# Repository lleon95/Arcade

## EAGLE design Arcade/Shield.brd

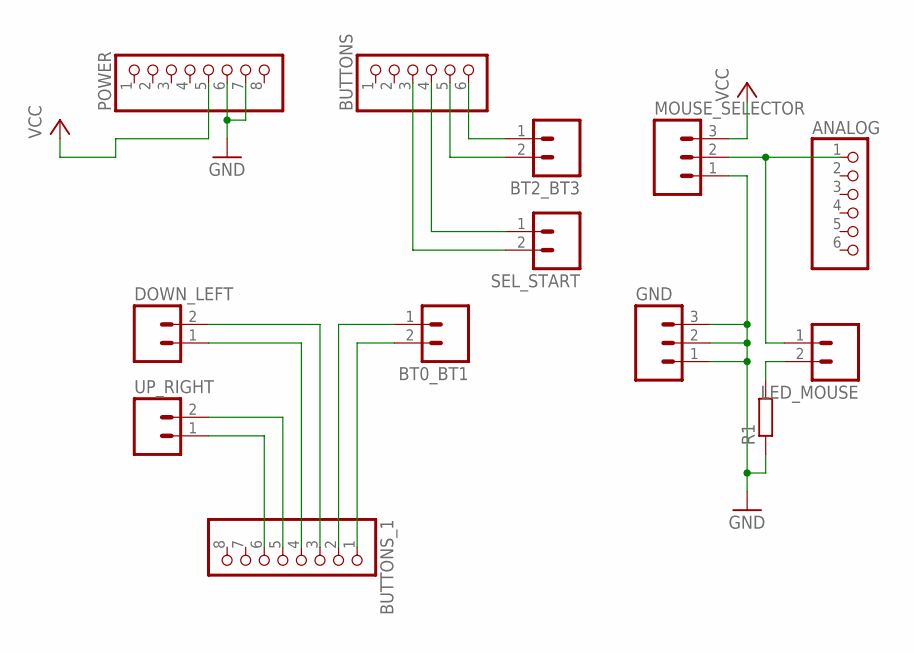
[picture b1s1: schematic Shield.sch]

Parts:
ANALOG: PINHD-1X6; 1X06
BT0_BT1, BT2_BT3: M023.5MM; SCREWTERMINAL-3.5MM-2
BUTTONS: PINHD-1X6; 1X06
BUTTONS_1: PINHD-1X8BIG; 1X08-BIG
DOWN_LEFT: M023.5MM; SCREWTERMINAL-3.5MM-2
GND: M03SCREW; SCREWTERMINAL-3.5MM-3
LED_MOUSE: M023.5MM; SCREWTERMINAL-3.5MM-2
MOUSE_SELECTOR: M03SCREW; SCREWTERMINAL-3.5MM-3
POWER: PINHD-1X8BIG; 1X08-BIG
R1: R-EU_0204/7; 0204/7
SEL_START: M023.5MM; SCREWTERMINAL-3.5MM-2
UP_RIGHT: M023.5MM; SCREWTERMINAL-3.5MM-2

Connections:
GND: GND.1, GND.2, GND.3, MOUSE_SELECTOR.1, POWER.6, POWER.7, R1.1
unnamed: BT0_BT1.2, BUTTONS_1.1
unnamed: BT0_BT1.1, BUTTONS_1.2
unnamed: BUTTONS_1.3, DOWN_LEFT.2
unnamed: BUTTONS_1.4, DOWN_LEFT.1
unnamed: BUTTONS_1.5, UP_RIGHT.2
unnamed: BUTTONS_1.6, UP_RIGHT.1
unnamed: BT2_BT3.1, BUTTONS.6
unnamed: BT2_BT3.2, BUTTONS.5
unnamed: BUTTONS.4, SEL_START.1
unnamed: BUTTONS.3, SEL_START.2
unnamed: ANALOG.1, LED_MOUSE.1, MOUSE_SELECTOR.2
unnamed: LED_MOUSE.2, R1.2
VCC: MOUSE_SELECTOR.3, POWER.5

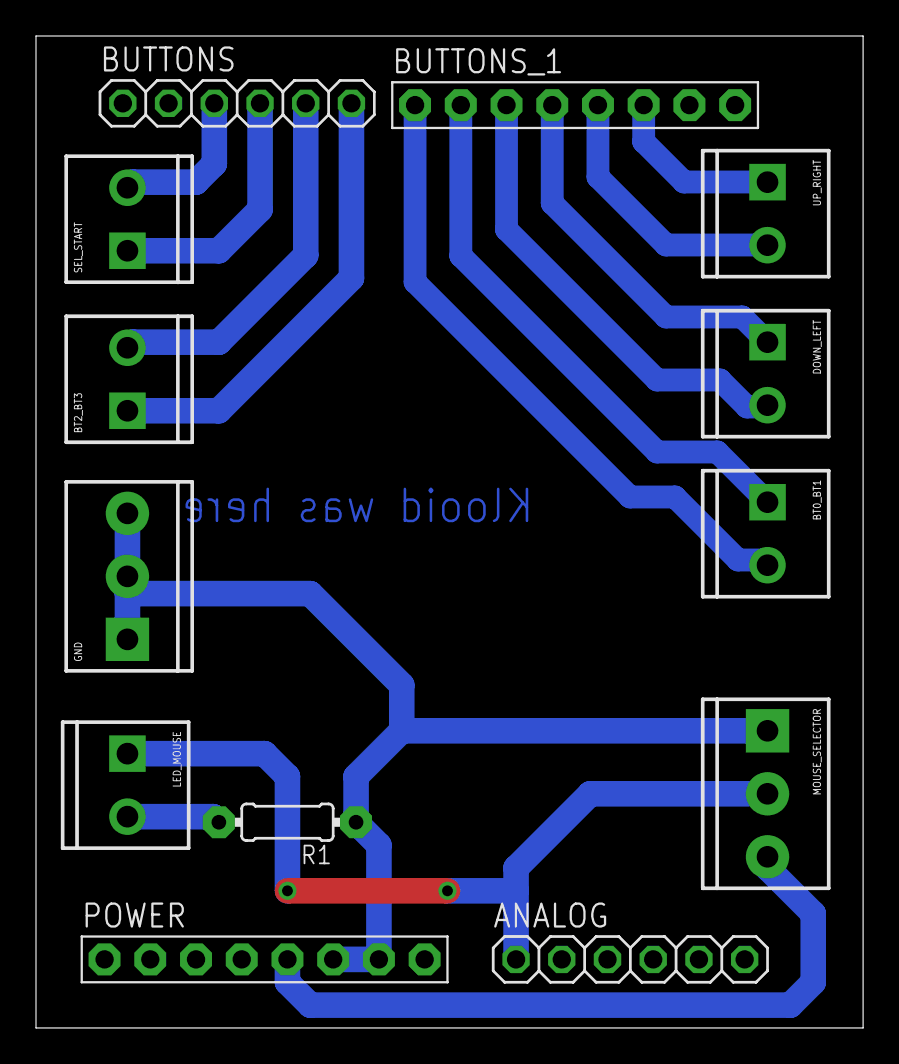
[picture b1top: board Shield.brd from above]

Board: 2 copper layers, 46.0 x 55.1 mm, 13 parts (0 on the bottom side), 14 nets.

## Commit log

2017-04-23 :tada: Added .gitattributes & .gitignore files
2017-04-23 1 version

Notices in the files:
parts and their libraries:
SparkFun-Connectors: Licensing: Creative Commons ShareAlike 4.0 International - https://creativecommons.org/licenses/by-sa/4.0
